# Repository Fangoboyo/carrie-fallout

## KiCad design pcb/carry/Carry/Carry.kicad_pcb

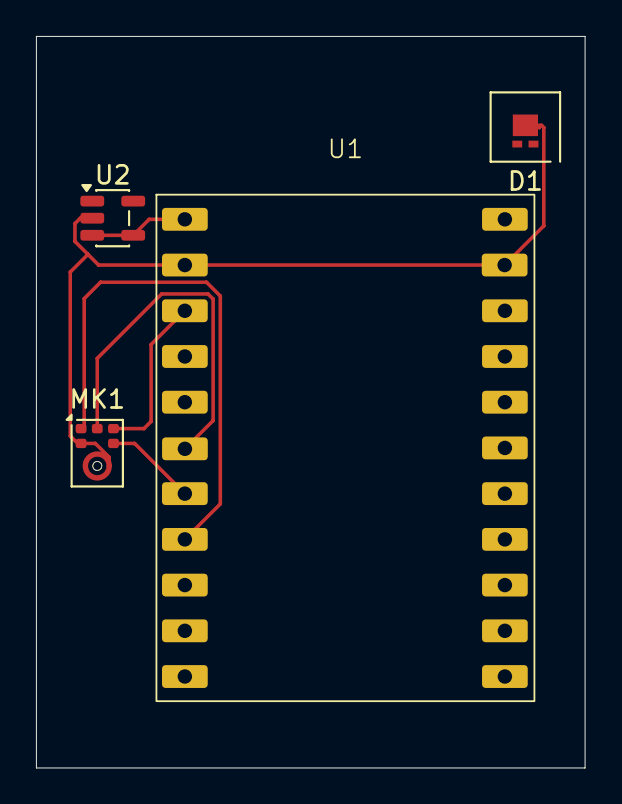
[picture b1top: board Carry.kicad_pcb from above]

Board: 2 copper layers, 30.5 x 40.6 mm, 4 parts (0 on the bottom side), 6 nets.

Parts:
D1: LED_Dual_AAK; LED-L1T2_LUMILEDS
MK1: SPH0645LM4H; Knowles_SPH0645LM4H-6_3.5x2.65mm
U1: Luckfox-Pico_Mini_B; Luckfox_Pico_Mini_B
U2: MCP73831-2-OT; SOT-23-5

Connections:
/MIC_DATA: MK1.6 (DATA), U1.6 (GPIO1_C0_d)
GND: D1.3 (K), MK1.2 (SEL), MK1.3 (GND), U1.2 (GND), U1.21 (GND), U2.2 (V_{SS})
unnamed: U1.1 (VBUS), U2.3 (V_{BAT}), U2.4 (V_{DD})
unnamed: MK1.4 (BCLK), U1.7 (GPIO1_C1_d)
unnamed: MK1.5 (VDD), U1.3 (VCC_3V3)
unnamed: MK1.1 (WS), U1.8 (GPIO1_C2_d)

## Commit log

2026-05-09 initial commit for docker dev environment setup with camera. code needs to reviewed
2026-05-09 Refactor software files into 1 folder
2026-05-11 Stop the lock message
    theres always this lock msg so this should allow me to use the github file as the one I always open. something like that
2026-05-12 made programatic recording start
2026-05-17 reorganized and added gpio button click detection
2026-05-18 finish "click to record"
2026-05-19 platform framework setup
2026-05-19 moved to react + shadcn instead of native JS
